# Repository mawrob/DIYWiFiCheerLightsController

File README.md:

# DIYWiFiCheerLightsController
DIY WiFi CheerLights controller using the Particle Photon

These files are currently in draft form and are being used as part of a class on how to use Eagle to design a PCB.

See here for details: http://www.mawrey.com/from-prototype-to-production-with-eagle-pcb-design/

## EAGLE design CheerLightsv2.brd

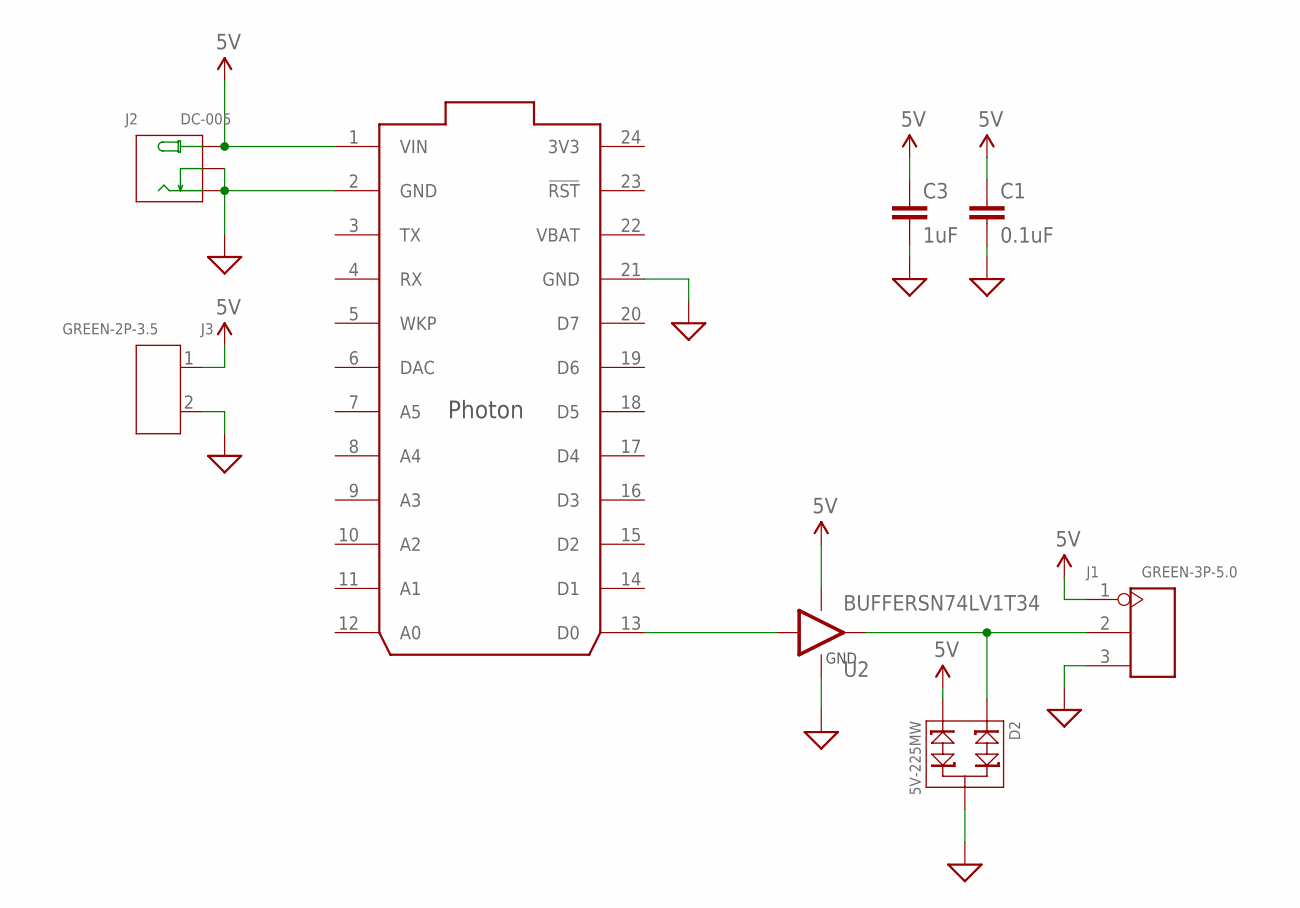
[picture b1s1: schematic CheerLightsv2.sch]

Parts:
C1: 0.1uF; 0805
C3: 1uF; 0805
D2: 5V-225MW; SOT-23; PARTNO TPD2E009DBZR
J1: GREEN-3P-5.0; H3-5.0-15.5X8.0MM; PARTNO 1935174
J2: DC-005; DCJ3P-14.2X11.0X9.0MM; PARTNO EJ508A
J3: GREEN-2P-3.5; H2-3.5-7.0X7.0MM
U1: PHOTON_WITH_HEADERS; PHOTON
U2: BUFFERSN74LV1T34; SOT23-5

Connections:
3V3: U1.24 (3V3)
5V: C1.1, C3.1, D2.2, J1.1, J2.+, J3.1, U1.1 (VIN), U2.5 (PWR)
DATA: U1.13 (D0), U2.2 (IN)
DOUT: D2.1, J1.2, U2.4 (OUT)
GND: C1.2, C3.2, D2.3, J1.3, J2.-1 (-), J2.-2 (CDN), J3.2, U1.2 (GND), U1.21 (GND), U2.3 (GND)
VBAT: U1.22 (VBAT)

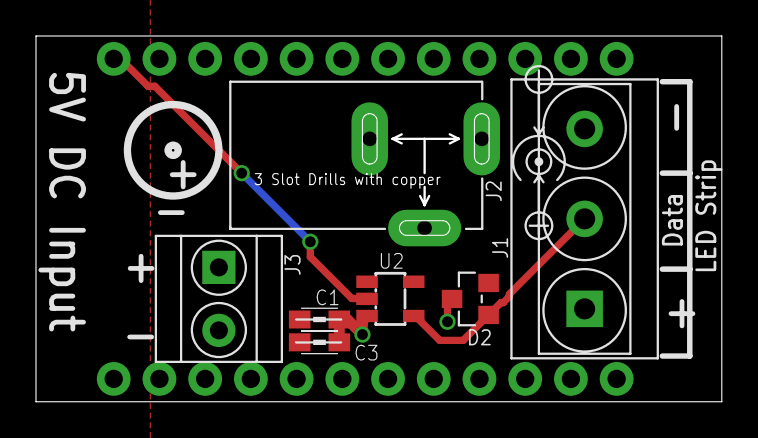
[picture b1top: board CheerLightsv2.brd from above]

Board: 2 copper layers, 38.0 x 20.2 mm, 8 parts (1 on the bottom side), 4 nets.

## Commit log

2017-03-15 Add files via upload
    Updated schematic and board files
2017-03-15 Add files via upload
    Lastest versions
2017-04-19 Create dru
2017-04-19 Add cam file
2017-04-19 Uploaded alternative design v2
2017-05-11 Add manufacturing files
2017-05-11 Gerber and drill files
2017-05-11 Latest Eagle files
2017-06-08 Links to files
2017-06-08 ulp for freerouting
2017-06-08 added ulp link
2017-06-08 Added test files to work with

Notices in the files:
parts and their libraries:
SparkFun-Aesthetics: Licensing: Creative Commons ShareAlike 4.0 International - https://creativecommons.org/licenses/by-sa/4.0
